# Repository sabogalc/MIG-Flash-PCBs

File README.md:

# MIG Flash PCBs & Models
This repository hosts KiCad projects and 3D printable replacement parts for the MIG Dumper and Flashcart PCBs. These files should prove very useful towards understanding the inner workings of the devices, especially with the schematics and boardview files. As-is, not much can be done with the board files since the original boards are programmed at the factory. The only way to currently get a working board from these files is by transplanting at minimum the FPGA and the microcontroller from an OEM MIG device to the new board.

> 
> The 8 pins seen above the USB-C port and to the right of the microcontroller in this photo are the ones used to program the board at the factory (see https://docs.espressif.com/projects/esp-idf/en/v5.2/esp32s2/api-guides/dfu.html for more information)

> 
> The flashcart PCB inside of the game enclosure.

Another useful resource found in this repo is the bill of materials for both devices. If you have a MIG device but a part on it has gone bad or is missing, this repository should assist with finding replacement resistors or capacitors of the correct value, or finding part numbers for components such as the toggle button on the Flashcart. For more information on either board, see their folders in the `KiCad Projects` directory.

The 3D models are compatible with original hardware and the PCBs in this repository. The recommended screws for the dumper are M2x8 and for the cartridge shell are M1.2x2. Both may printed in filament or resin, though resin is recommended for the cartridge shell to better reproduce sub-mm features.

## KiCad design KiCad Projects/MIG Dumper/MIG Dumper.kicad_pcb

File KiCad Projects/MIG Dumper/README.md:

# MIG Dumper

### Overview
This is a very straightforward board design. The FPGA is is the first point of contact with the cartridge, and it takes care of direct communication with the data and clock lines in order to be able to read the onboard cartridge data. The microcontroller then takes this data from the FPGA, and it relays it to the SD card to USB adapter, presumably through SPI (reference [here](https://switchbrew.org/wiki/Gamecard#Protocol)). With data moving to and from the FPGA/microcontroller in SPI, it is very simple to configure the board as if it were reading an SD card, after which the dumper allows the files to be read by any USB-enabled device.

### Ordering Specifications
The original board is a standard 1.6mm thick board, and all other options (soldermask, surface finish, etc.) can be customized to your liking. Please note that if you are using the OEM enclosure, the 4.7uF capacitor for C29 in the included Digikey/Mouser BOMs is too tall to allow for it to fully close. The capacitor on the original board is 0.85mm tall, but the one I included is 1.6mm tall.

### Component Measurements and BOM Discrepancies
I measured the components to the best of my ability, but there may be slight discrepancies. For example, the aforementioned 4.7uF capacitor was read in real life to be 4.5uF, but I could not find a 1206 4.5uF capacitor on either Digikey or Mouser. As such, the BOMs have some substitutions, such as 100nF capacitors instead of 110nF capacitors, but the measurements in the schematic and PCB are what most align with what I measured in real life. For capacitors in the pF range that I could not measure, I referenced the datasheets for the [ECS-400-10-37B2-CKY-TR](https://ecsxtal.com/store/pdf/ECX-1637B2.pdf) and [MAX20022ATIA+](https://www.analog.com/media/en/technical-documentation/data-sheets/max20021-max20022.pdf) to obtain these values.

Additionally, the SD card to USB adapter chip and the cartridge reader are not present in the BOMs because neither part is available on Digikey or Mouser, but you can purchase both of them from AliExpress.

[GL823K-HCY04 chip](https://www.aliexpress.com/item/3256805047594623.html)

[Cartridge reader](https://www.aliexpress.com/item/3256804487003304.html)

### Can I use these designs to manufacture my own MIG Dumper?
Yes and no. I have succesfully transplanted all the parts of an original Dumper to this PCB, and it works perfectly. Building it from scratch with the parts from the included `.csv` and `.xlsx` BOMs does not work, but if you substitute in an OEM FPGA and ESP32, then it works. This is because the firmware for these chips is programmed and encrypted at the factory, as specified in the main landing page's `README`.

While it may be possible to break this encryption (see [here](https://hackaday.com/2024/01/15/breaking-the-flash-encryption-feature-of-espressifs-microcontrollers/)), I am a hardware engineer and not very interested in delving into the firmware side of things. However, I will include a schematic for a programmer board below should anyone want to embark on that journey. The instructions for the boot sequence needed are found at https://docs.espressif.com/projects/esp-idf/en/v5.2/esp32s2/api-guides/dfu.html in the bootloader mode note.

Below is a photo of the board from this repository screwed into the enclosure and reading a gamecard.

### KiCad 3D View
Below are screenshots of the board from KiCad's 3D board viewer.

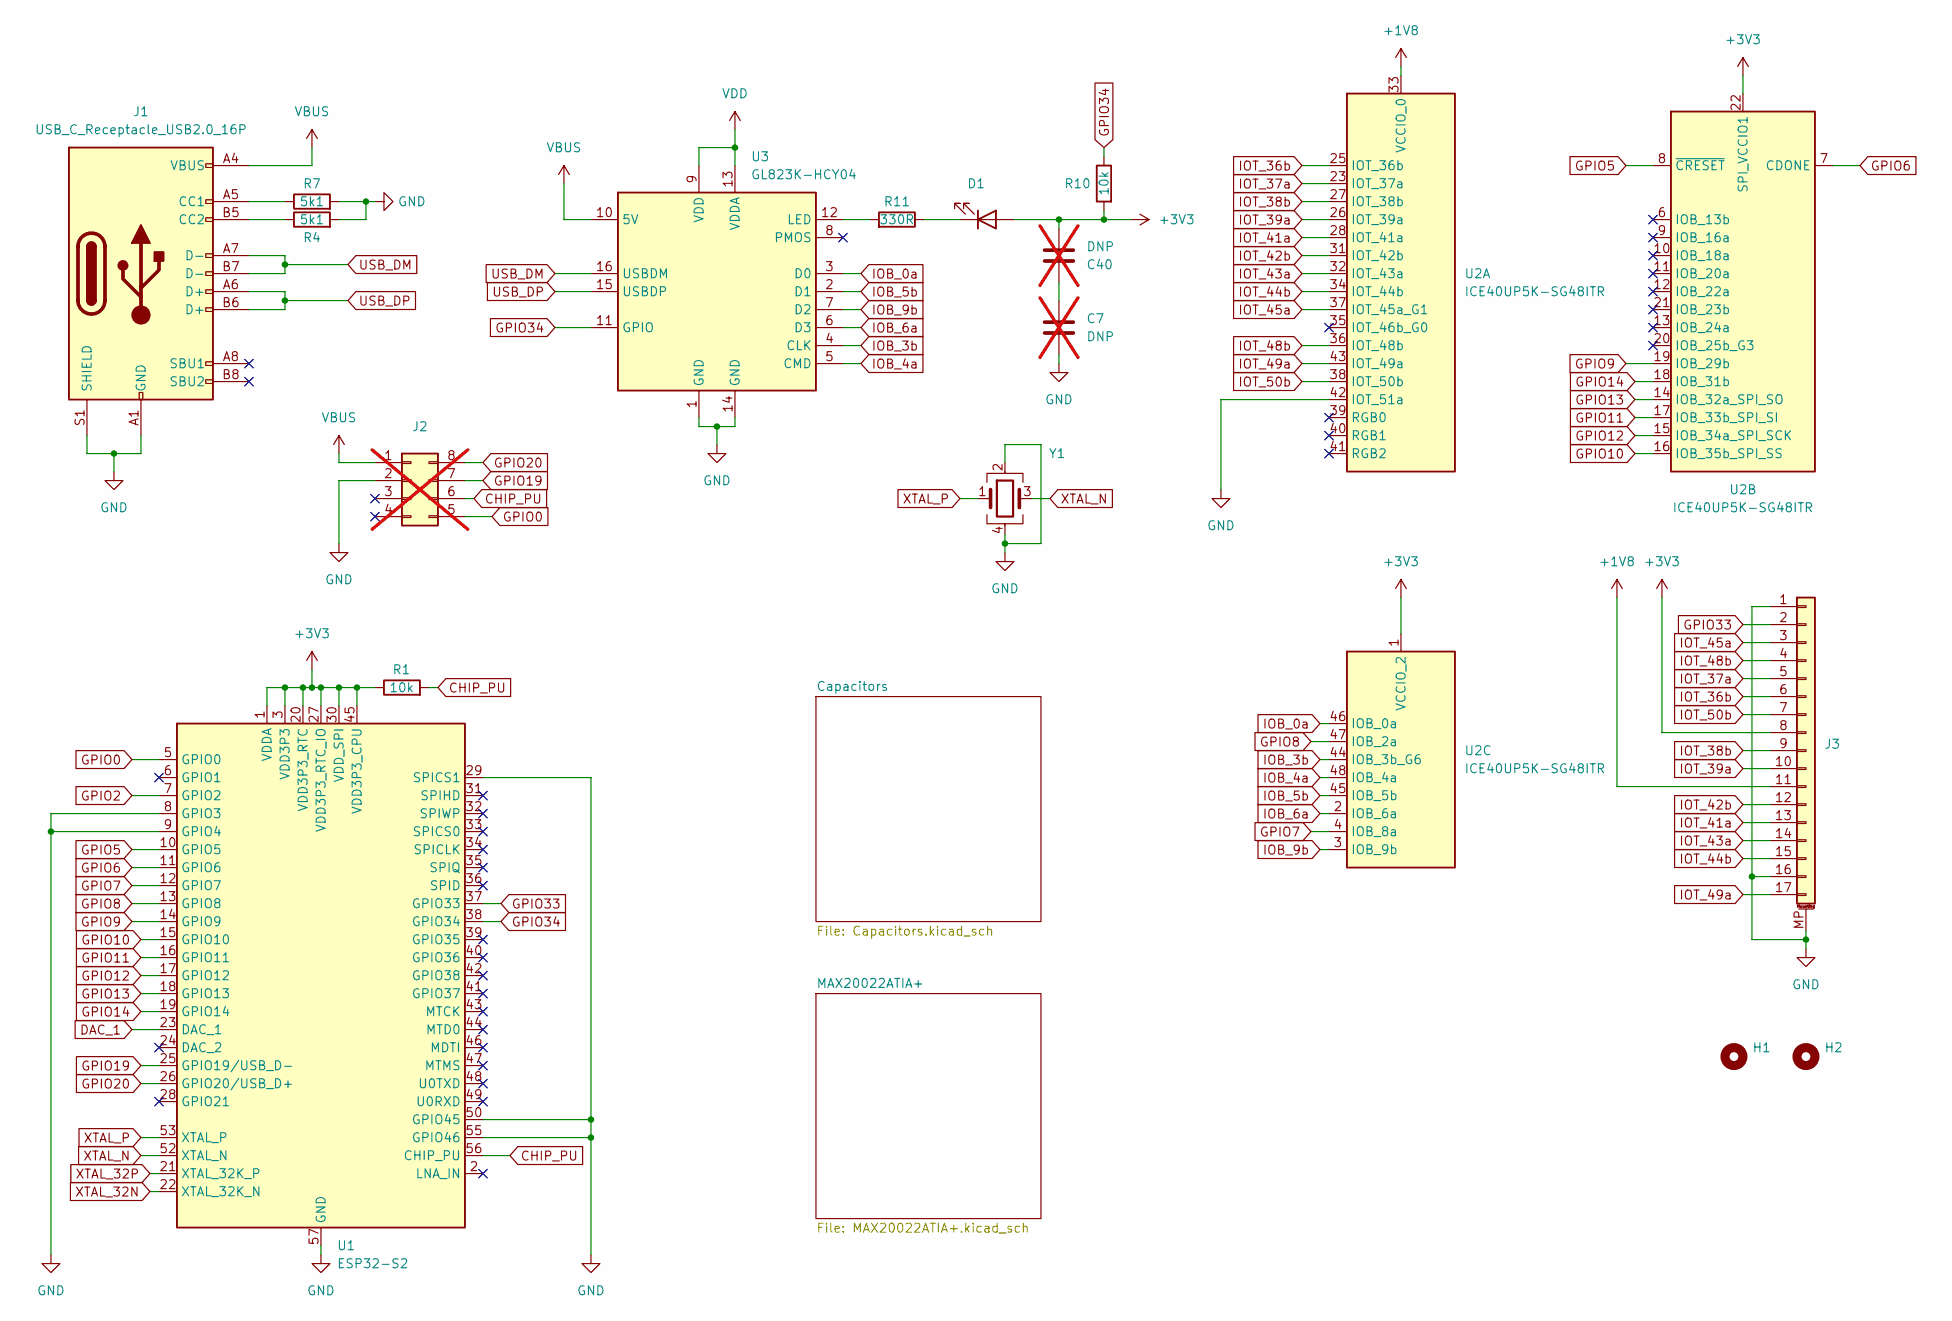
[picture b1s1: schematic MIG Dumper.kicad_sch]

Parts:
C7: DNP; C_1206_3216Metric_Pad1.33x1.80mm_HandSolder; not fitted
C40: DNP; C_0603_1608Metric; not fitted
D1: APT3216LSECK/J3-PRV; LED_1206_3216Metric_Pad1.42x1.75mm_HandSolder
H1, H2: MountingHole; MountingHole_2.2mm_M2_DIN965_Pad_TopBottom
J1: USB_C_Receptacle_USB2.0_16P; USB_C_Receptacle_GCT_USB4105-xx-A_16P_TopMnt_Horizontal
J2: Conn_02x04_Counter_Clockwise; PinHeader_2x04_P1.27mm_Vertical; not fitted
J3: Conn_01x17_MountingPin; Switch_Cartridge
R1, R10: 10k; R_0603_1608Metric
R4, R7: 5k1; R_0603_1608Metric
R11: 330R; R_0603_1608Metric
U1: ESP32-S2; QFN-56-1EP_7x7mm_P0.4mm_EP4x4mm
U2: ICE40UP5K-SG48ITR; QFN-48-1EP_7x7mm_P0.5mm_EP5.15x5.15mm
U3: GL823K-HCY04; SSOP-16_3.9x4.9mm_P0.635mm
Y1: ECS-400-10-37B2-CKY-TR; Crystal_SMD_SeikoEpson_FA128-4Pin_2.0x1.6mm

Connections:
+1V8: J3.11, U2.33 (VCCIO_0); also elsewhere on the board
+3V3: C40.2, D1.2 (A), J3.8, R1.1, R10.2, U1.1 (VDDA), U1.3 (VDD3P3), U1.4 (VDD3P3), U1.20 (VDD3P3_RTC), U1.27 (VDD3P3_RTC_IO), U1.30 (VDD_SPI), U1.45 (VDD3P3_CPU), U1.51 (VDDA), U1.54 (VDDA), U2.1 (VCCIO_2), U2.22 (SPI_VCCIO1); also elsewhere on the board
CHIP_PU: J2.6, R1.2, U1.56 (CHIP_PU)
DAC_1: U1.23 (DAC_1); also elsewhere on the board
GND: C7.2, J1.A1 (GND), J1.A12 (GND), J1.B1 (GND), J1.B12 (GND), J1.S1 (SHIELD), J2.2, J3.1, J3.16, J3.MP (MountPin), R4.2, R7.2, U1.8 (GPIO3), U1.9 (GPIO4), U1.29 (SPICS1), U1.50 (GPIO45), U1.55 (GPIO46), U1.57 (GND), U2.42 (IOT_51a), U3.1 (GND), U3.14 (GND), Y1.2, Y1.4; also elsewhere on the board
GPIO0: J2.5, U1.5 (GPIO0)
GPIO2: U1.7 (GPIO2); also elsewhere on the board
GPIO5: U1.10 (GPIO5), U2.8 (~CRESET)
GPIO6: U1.11 (GPIO6), U2.7 (CDONE)
GPIO7: U1.12 (GPIO7), U2.4 (IOB_8a)
GPIO8: U1.13 (GPIO8), U2.47 (IOB_2a)
GPIO9: U1.14 (GPIO9), U2.19 (IOB_29b)
GPIO10: U1.15 (GPIO10), U2.16 (IOB_35b_SPI_SS)
GPIO11: U1.16 (GPIO11), U2.17 (IOB_33b_SPI_SI)
GPIO12: U1.17 (GPIO12), U2.15 (IOB_34a_SPI_SCK)
GPIO13: U1.18 (GPIO13), U2.14 (IOB_32a_SPI_SO)
GPIO14: U1.19 (GPIO14), U2.18 (IOB_31b)
GPIO19: J2.7, U1.25 (GPIO19/USB_D-)
GPIO20: J2.8, U1.26 (GPIO20/USB_D+)
GPIO33: J3.2, U1.37 (GPIO33)
GPIO34: R10.1, U1.38 (GPIO34), U3.11 (GPIO)
IOB_0a: U2.46 (IOB_0a), U3.3 (D0)
IOB_3b: U2.44 (IOB_3b_G6), U3.4 (CLK)
IOB_4a: U2.48 (IOB_4a), U3.5 (CMD)
IOB_5b: U2.45 (IOB_5b), U3.2 (D1)
IOB_6a: U2.2 (IOB_6a), U3.6 (D3)
IOB_9b: U2.3 (IOB_9b), U3.7 (D2)
IOT_36b: J3.6, U2.25 (IOT_36b)
IOT_37a: J3.5, U2.23 (IOT_37a)
IOT_38b: J3.9, U2.27 (IOT_38b)
IOT_39a: J3.10, U2.26 (IOT_39a)
IOT_41a: J3.13, U2.28 (IOT_41a)
IOT_42b: J3.12, U2.31 (IOT_42b)
IOT_43a: J3.14, U2.32 (IOT_43a)
IOT_44b: J3.15, U2.34 (IOT_44b)
IOT_45a: J3.3, U2.37 (IOT_45a_G1)
IOT_48b: J3.4, U2.36 (IOT_48b)
IOT_49a: J3.17, U2.43 (IOT_49a)
IOT_50b: J3.7, U2.38 (IOT_50b)
unnamed: C7.1, C40.1
unnamed: D1.1 (K), R11.1
unnamed: J1.A5 (CC1), R7.1
unnamed: J1.B5 (CC2), R4.1
unnamed: R11.2, U3.12 (LED)
USB_DM: J1.A7 (D-), J1.B7 (D-), U3.16 (USBDM)
USB_DP: J1.A6 (D+), J1.B6 (D+), U3.15 (USBDP)
VBUS: J1.A4 (VBUS), J1.A9 (VBUS), J1.B4 (VBUS), J1.B9 (VBUS), J2.1, U3.10 (5V); also elsewhere on the board
VDD: U3.9 (VDD), U3.13 (VDDA); also elsewhere on the board
XTAL_32N: U1.22 (XTAL_32K_N); also elsewhere on the board
XTAL_32P: U1.21 (XTAL_32K_P); also elsewhere on the board
XTAL_N: U1.52 (XTAL_N), Y1.3; also elsewhere on the board
XTAL_P: U1.53 (XTAL_P), Y1.1; also elsewhere on the board

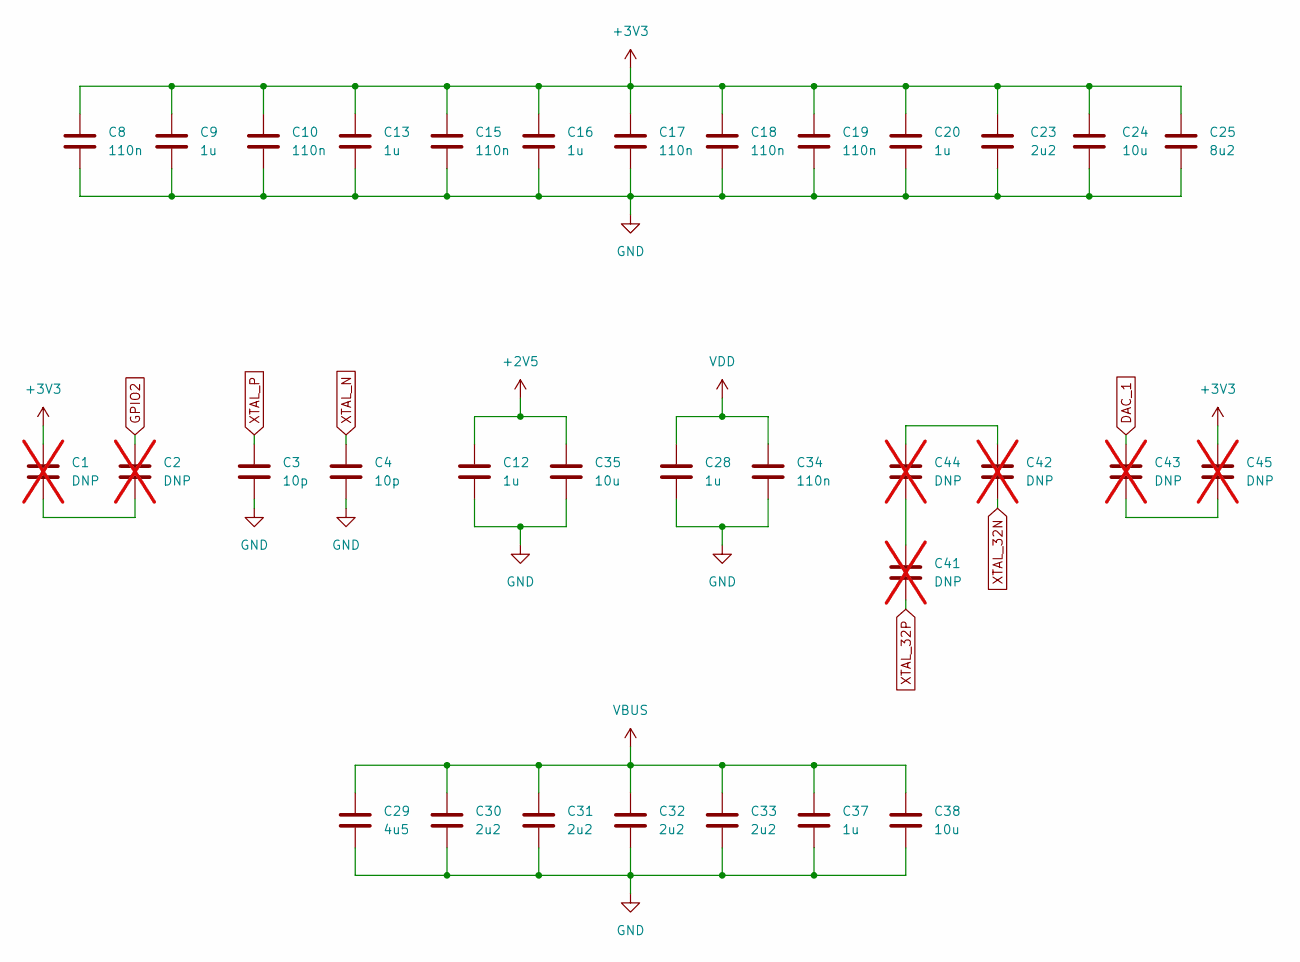
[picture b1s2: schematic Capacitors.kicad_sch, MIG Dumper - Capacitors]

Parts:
C1: DNP; C_1206_3216Metric_Pad1.33x1.80mm_HandSolder; not fitted
C2, C41, C42, C43: DNP; C_0603_1608Metric; not fitted
C3, C4: 10p; C_0603_1608Metric
C8, C10, C15, C17, C18, C19, C34: 110n; C_0603_1608Metric
C9, C12, C13, C16, C20, C28, C37: 1u; C_0603_1608Metric
C23, C30, C31, C32, C33: 2u2; C_0603_1608Metric
C24, C35, C38: 10u; C_1206_3216Metric_Pad1.33x1.80mm_HandSolder
C25: 8u2; C_1206_3216Metric_Pad1.33x1.80mm_HandSolder
C29: 4u5; C_1206_3216Metric_Pad1.33x1.80mm_HandSolder
C44, C45: DNP; C_0201_0603Metric; not fitted

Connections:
+2V5: C12.1, C35.1; also elsewhere on the board
+3V3: C1.1, C8.1, C9.1, C10.1, C13.1, C15.1, C16.1, C17.1, C18.1, C19.1, C20.1, C23.1, C24.1, C25.1, C45.1; also elsewhere on the board
DAC_1: C43.2; also elsewhere on the board
GND: C3.2, C4.2, C8.2, C9.2, C10.2, C12.2, C13.2, C15.2, C16.2, C17.2, C18.2, C19.2, C20.2, C23.2, C24.2, C25.2, C28.2, C29.2, C30.2, C31.2, C32.2, C33.2, C34.2, C35.2, C37.2, C38.2; also elsewhere on the board
GPIO2: C2.1; also elsewhere on the board
unnamed: C1.2, C2.2
unnamed: C41.1, C44.1
unnamed: C42.1, C44.2
unnamed: C43.1, C45.2
VBUS: C29.1, C30.1, C31.1, C32.1, C33.1, C37.1, C38.1; also elsewhere on the board
VDD: C28.1, C34.1; also elsewhere on the board
XTAL_32N: C42.2; also elsewhere on the board
XTAL_32P: C41.2; also elsewhere on the board
XTAL_N: C4.1; also elsewhere on the board
XTAL_P: C3.1; also elsewhere on the board

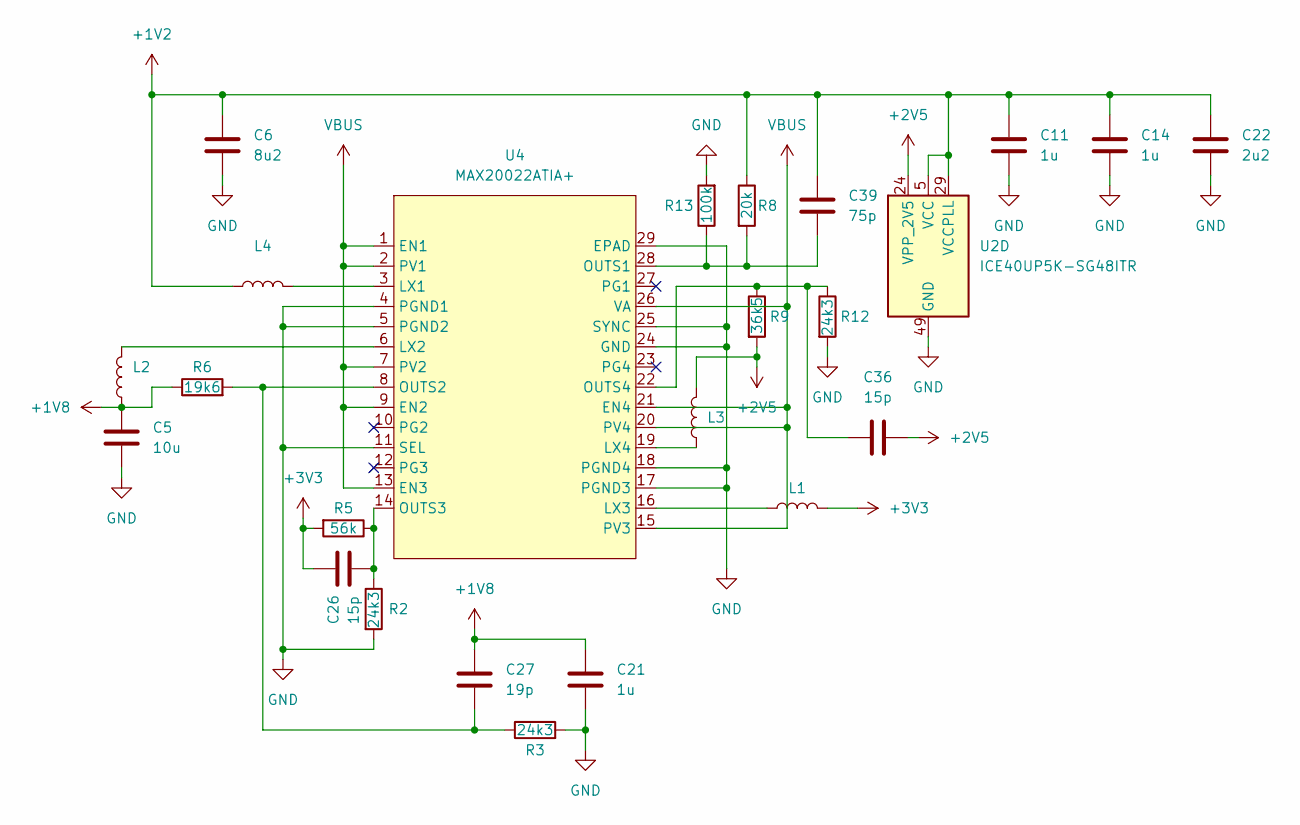
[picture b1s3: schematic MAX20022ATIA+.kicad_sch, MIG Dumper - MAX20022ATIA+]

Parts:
C5: 10u; C_1206_3216Metric_Pad1.33x1.80mm_HandSolder
C6: 8u2; C_1206_3216Metric_Pad1.33x1.80mm_HandSolder
C11, C14, C21: 1u; C_0603_1608Metric
C22: 2u2; C_0603_1608Metric
C26, C36: 15p; C_0603_1608Metric
C27: 19p; C_0603_1608Metric
C39: 75p; C_0603_1608Metric
L1, L2, L3, L4: LQM21PN1R5MEHD; L_0805_2012Metric_Pad1.15x1.40mm_HandSolder
R2, R3, R12: 24k3; R_0603_1608Metric
R5: 56k; R_0603_1608Metric
R6: 19k6; R_0603_1608Metric
R8: 20k; R_0603_1608Metric
R9: 36k5; R_0603_1608Metric
R13: 100k; R_0603_1608Metric
U2: ICE40UP5K-SG48ITR; QFN-48-1EP_7x7mm_P0.5mm_EP5.15x5.15mm
U4: MAX20022ATIA+; TQFN-28-1EP_5x5mm_P0.5mm_EP2.7x2.7mm

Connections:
+1V2: C6.1, C11.1, C14.1, C22.1, C39.1, L4.1, R8.1, U2.5 (VCC), U2.29 (VCCPLL), U2.30 (VCC)
+1V8: C5.1, C21.1, C27.1, L2.1, R6.1; also elsewhere on the board
+2V5: C36.1, L3.2, R9.2, U2.24 (VPP_2V5); also elsewhere on the board
+3V3: C26.1, L1.2, R5.2; also elsewhere on the board
GND: C5.2, C6.2, C11.2, C14.2, C21.2, C22.2, R2.2, R3.2, R12.2, R13.2, U2.49 (GND), U4.4 (PGND1), U4.5 (PGND2), U4.11 (SEL), U4.17 (PGND3), U4.18 (PGND4), U4.24 (GND), U4.25 (SYNC), U4.29 (EPAD); also elsewhere on the board
unnamed: L4.2, U4.3 (LX1)
unnamed: L2.2, U4.6 (LX2)
unnamed: L1.1, U4.16 (LX3)
unnamed: L3.1, U4.19 (LX4)
unnamed: C39.2, R8.2, R13.1, U4.28 (OUTS1)
unnamed: C27.2, R3.1, R6.2, U4.8 (OUTS2)
unnamed: C26.2, R2.1, R5.1, U4.14 (OUTS3)
unnamed: C36.2, R9.1, R12.1, U4.22 (OUTS4)
VBUS: U4.1 (EN1), U4.2 (PV1), U4.7 (PV2), U4.9 (EN2), U4.13 (EN3), U4.15 (PV3), U4.20 (PV4), U4.21 (EN4), U4.26 (VA); also elsewhere on the board

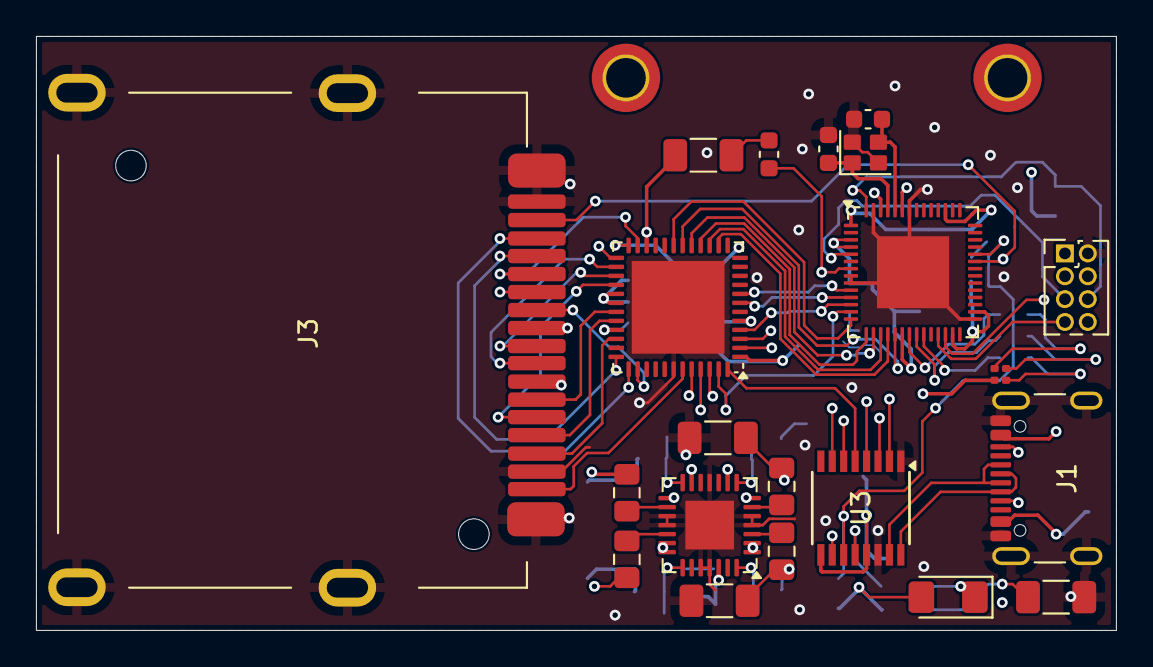
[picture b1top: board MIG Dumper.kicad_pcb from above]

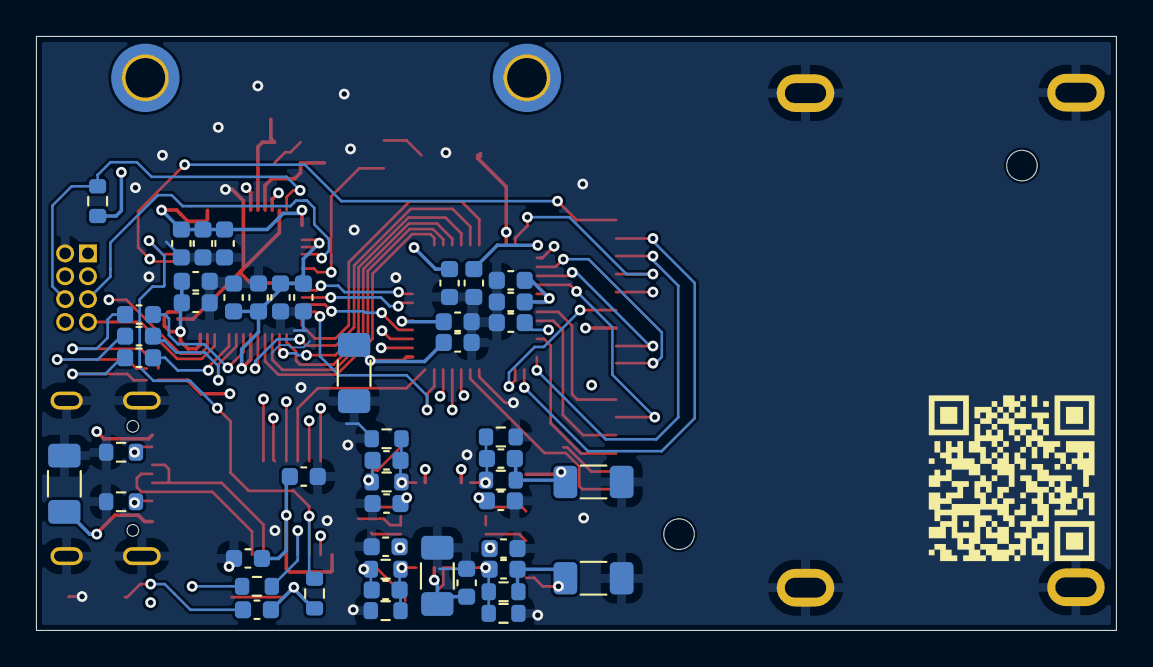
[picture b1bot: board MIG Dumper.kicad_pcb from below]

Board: 4 copper layers, 60.0 x 33.0 mm, 73 parts (49 on the bottom side), 66 nets.

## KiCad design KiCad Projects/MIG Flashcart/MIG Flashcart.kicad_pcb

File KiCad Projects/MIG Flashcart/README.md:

# MIG Flashcart

### Overview
The Flashcart board is very compact, and it is a bit challenging to solder it by hand. Most of the passive components are the 0201 size, and the 0404 RGB LED in the top right is also extremely small. Additionally, the vias have been trimmed down to a 0.2mm size to accommodate the board's routing.

A series of leaks in July 2021 made the low-level hardware of the Switch game cartridge reader public, and it is powered by an ASIC called [Lotus3](https://switchbrew.org/wiki/Lotus3). I don't know much about how this chip/protocol works, but the FPGA and microcontroller in this flashcart are programmed to communicate on this custom interface. 

### Ordering Specifications
To ensure this board fits in the game enclosure and that it can be read, it should be ordered as a 0.8mm thick board with an ENIG finish. All other options can be left as their default.

### Component Measurements and BOM Discrepancies
I measured the components to the best of my ability, but there may be slight discrepancies. For example, I found it odd that 12 of the capacitors measured as 0.82uF and 4 of them measured as 0.88uF. I suspect that all of them are 0.82uF, and imperfections in the measurements caused the 4 outliers to read higher values. Even so, they were consistently measuring high enough that I felt it best to mark them as 0.88uF in the schematic. This point is a bit moot, however, because I could not find any 0201 capacitors on either Digikey or Mouser for 0.82uF or 0.88uF. As such, the BOMs have some substitutions, such as 1uF capacitors in place of the 0.82uF and 0.88uF ones, but the measurements in the schematic and PCB are what most align with what I measured in real life.

### Can I use these designs to manufacture my own MIG Flashcart?
The answer is the same as in [the corresponding section of the Dumper's README](https://github.com/sabogalc/MIG-Flash-PCBs/tree/main/KiCad%20Projects/MIG%20Dumper#can-i-use-these-designs-to-manufacture-my-own-mig-dumper). Due to the firmware encryption on the original boards, making this board from scratch (e.g. without transplanting the original μC and FPGA) proves to be a bit of a challenge.

Importantly though, the programmer board schematic I made for the Dumper will not work for the Flashcart as-is since the Flashcart has no 5V/VBUS signal. The programmer board would need to be modified to have an onboard 3.3V regulator, and then with this signal on the Flashcart's VCC breakout signal, it should work. Should anyone make that programmer board and want to write their own firmware, the instructions for accomplishing this can be found on [Espressif's website in the bootloader mode note](https://docs.espressif.com/projects/esp-idf/en/v5.2/esp32s2/api-guides/dfu.html).

I have assembled this board with parts from the included BOM and confirmed that it works when using the chips from an OEM MIG Flashcart. If you are using the parts from the BOM, the LED has a pin 1 indicator which I will show in a photo below. Make sure that the white squre between the two gold pins is facing into the board towards the crystal oscillator.

Below are some photos of the board from this repository in the flashcart enclosure.

> 
> The cartridge reading a game in the Switch and showing a green status LED.

### KiCad 3D View
Below are screenshots of the board from KiCad's 3D board viewer.

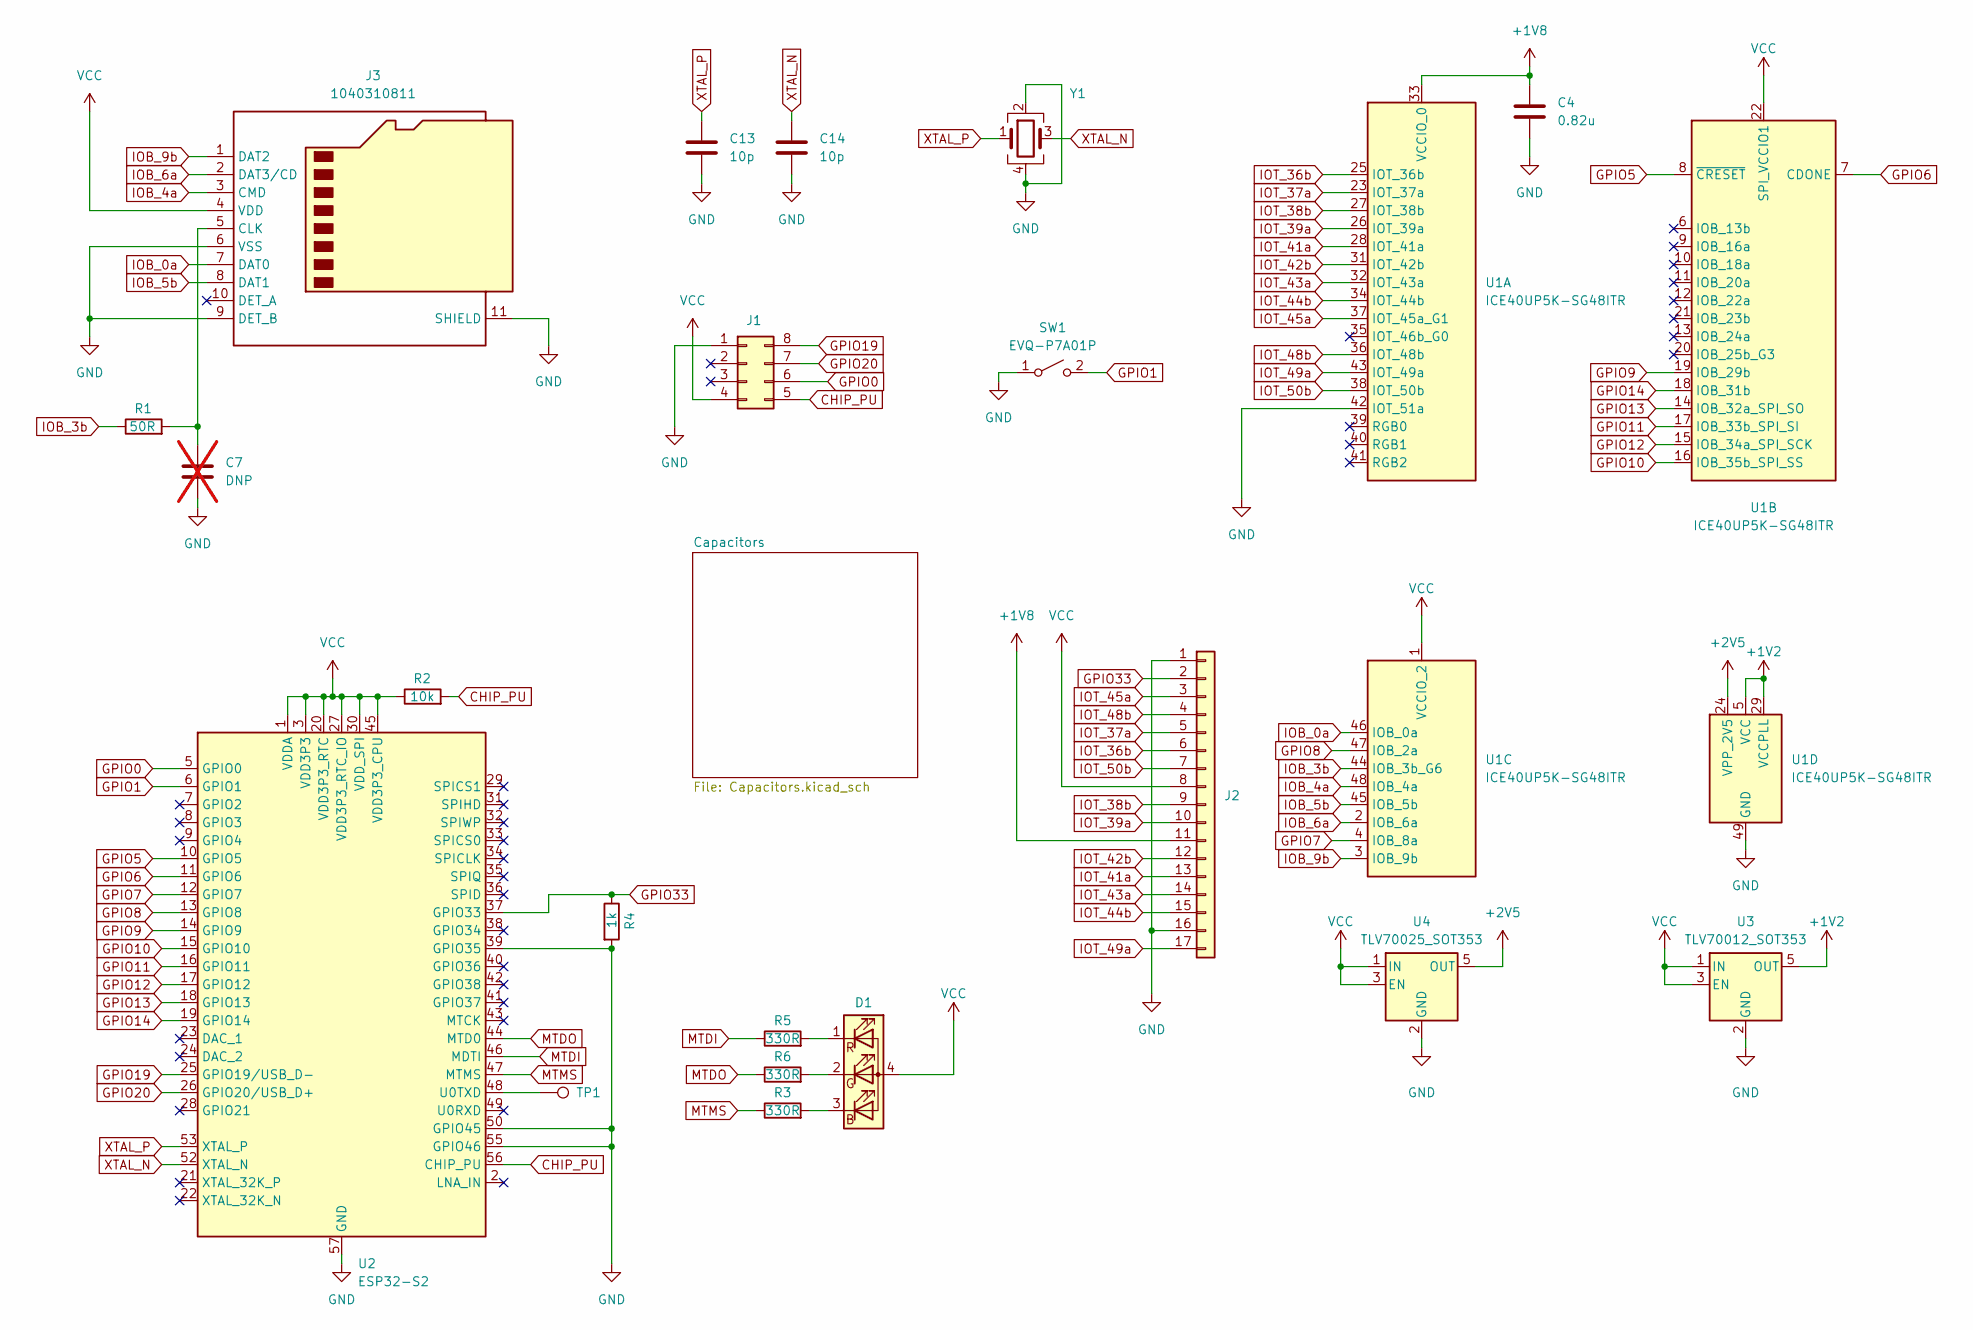
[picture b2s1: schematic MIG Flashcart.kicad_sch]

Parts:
C4: 0.82u; C_0201_0603Metric
C7: DNP; C_0201_0603Metric; not fitted
C13, C14: 10p; C_0201_0603Metric
D1: UHD111A-FKA-C3K23E1L3VG5ZB3Z3; SMD4_UHD111A-FKA_CRW
J1: Conn_02x04_Counter_Clockwise; PinSocket_2x04_P1.27mm_Vertical_SMD
J2: Conn_01x17; Cartridge_Pins
J3: 1040310811; microSD_HC_Molex_104031-0811
R1: 50R; R_0201_0603Metric
R2: 10k; R_0201_0603Metric
R3, R5, R6: 330R; R_0201_0603Metric
R4: 1k; R_0201_0603Metric
SW1: EVQ-P7A01P; SW_SPST_EVQP7A
TP1: TestPoint; TestPoint_Pad_D0.5mm
U1: ICE40UP5K-SG48ITR; QFN-48-1EP_7x7mm_P0.5mm_EP5.15x5.15mm
U2: ESP32-S2; QFN-56-1EP_7x7mm_P0.4mm_EP4x4mm
U3: TLV70012_SOT353; SOT-353_SC-70-5
U4: TLV70025_SOT353; SOT-353_SC-70-5
Y1: ECS-400-10-37B2-CKY-TR; Crystal_SMD_SeikoEpson_FA128-4Pin_2.0x1.6mm

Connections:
+1V2: U1.5 (VCC), U1.29 (VCCPLL), U1.30 (VCC), U3.5 (OUT); also elsewhere on the board
+1V8: C4.1, J2.11, U1.33 (VCCIO_0)
+2V5: U1.24 (VPP_2V5), U4.5 (OUT); also elsewhere on the board
CHIP_PU: J1.5, R2.2, U2.56 (CHIP_PU)
GND: C4.2, C7.2, C13.2, C14.2, J1.1, J2.1, J2.16, J3.6 (VSS), J3.9 (DET_B), J3.11 (SHIELD), R4.2, SW1.1 (A), U1.42 (IOT_51a), U1.49 (GND), U2.39 (GPIO35), U2.50 (GPIO45), U2.55 (GPIO46), U2.57 (GND), U3.2 (GND), U4.2 (GND), Y1.2, Y1.4; also elsewhere on the board
GPIO0: J1.6, U2.5 (GPIO0)
GPIO1: SW1.2 (B), U2.6 (GPIO1)
GPIO5: U1.8 (~CRESET), U2.10 (GPIO5)
GPIO6: U1.7 (CDONE), U2.11 (GPIO6)
GPIO7: U1.4 (IOB_8a), U2.12 (GPIO7)
GPIO8: U1.47 (IOB_2a), U2.13 (GPIO8)
GPIO9: U1.19 (IOB_29b), U2.14 (GPIO9)
GPIO10: U1.16 (IOB_35b_SPI_SS), U2.15 (GPIO10)
GPIO11: U1.17 (IOB_33b_SPI_SI), U2.16 (GPIO11)
GPIO12: U1.15 (IOB_34a_SPI_SCK), U2.17 (GPIO12)
GPIO13: U1.14 (IOB_32a_SPI_SO), U2.18 (GPIO13)
GPIO14: U1.18 (IOB_31b), U2.19 (GPIO14)
GPIO19: J1.8, U2.25 (GPIO19/USB_D-)
GPIO20: J1.7, U2.26 (GPIO20/USB_D+)
GPIO33: J2.2, R4.1, U2.37 (GPIO33)
IOB_0a: J3.7 (DAT0), U1.46 (IOB_0a)
IOB_3b: R1.1, U1.44 (IOB_3b_G6)
IOB_4a: J3.3 (CMD), U1.48 (IOB_4a)
IOB_5b: J3.8 (DAT1), U1.45 (IOB_5b)
IOB_6a: J3.2 (DAT3/CD), U1.2 (IOB_6a)
IOB_9b: J3.1 (DAT2), U1.3 (IOB_9b)
IOT_36b: J2.6, U1.25 (IOT_36b)
IOT_37a: J2.5, U1.23 (IOT_37a)
IOT_38b: J2.9, U1.27 (IOT_38b)
IOT_39a: J2.10, U1.26 (IOT_39a)
IOT_41a: J2.13, U1.28 (IOT_41a)
IOT_42b: J2.12, U1.31 (IOT_42b)
IOT_43a: J2.14, U1.32 (IOT_43a)
IOT_44b: J2.15, U1.34 (IOT_44b)
IOT_45a: J2.3, U1.37 (IOT_45a_G1)
IOT_48b: J2.4, U1.36 (IOT_48b)
IOT_49a: J2.17, U1.43 (IOT_49a)
IOT_50b: J2.7, U1.38 (IOT_50b)
MTDI: R5.1, U2.46 (MDTI)
MTDO: R6.1, U2.44 (MTD0)
MTMS: R3.1, U2.47 (MTMS)
unnamed: D1.3 (BK), R3.2
unnamed: D1.2 (GK), R6.2
unnamed: D1.1 (RK), R5.2
unnamed: C7.1, J3.5 (CLK), R1.2
unnamed: TP1.1, U2.48 (U0TXD)
VCC: D1.4 (A), J1.4, J2.8, J3.4 (VDD), R2.1, U1.1 (VCCIO_2), U1.22 (SPI_VCCIO1), U2.1 (VDDA), U2.3 (VDD3P3), U2.4 (VDD3P3), U2.20 (VDD3P3_RTC), U2.27 (VDD3P3_RTC_IO), U2.30 (VDD_SPI), U2.45 (VDD3P3_CPU), U2.51 (VDDA), U2.54 (VDDA), U3.1 (IN), U3.3 (EN), U4.1 (IN), U4.3 (EN); also elsewhere on the board
XTAL_N: C14.1, U2.52 (XTAL_N), Y1.3
XTAL_P: C13.1, U2.53 (XTAL_P), Y1.1

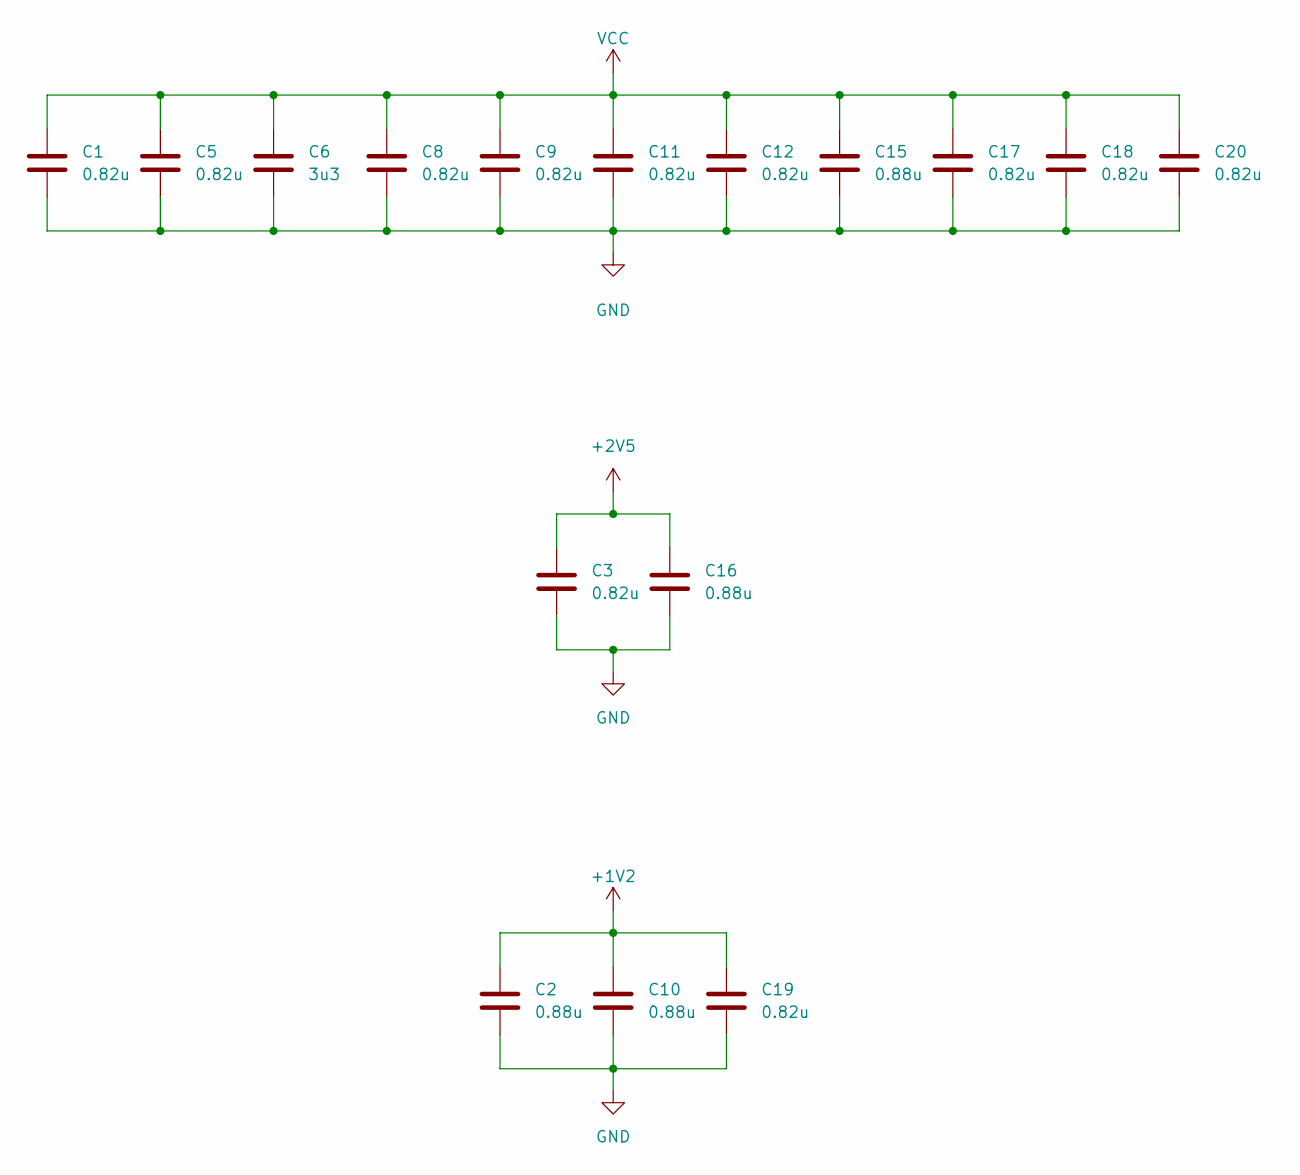
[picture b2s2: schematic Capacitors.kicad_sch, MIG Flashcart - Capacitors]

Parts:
C1, C3, C5, C8, C9, C11, C12, C17, C18, C19, C20: 0.82u; C_0201_0603Metric
C2, C10, C15, C16: 0.88u; C_0201_0603Metric
C6: 3u3; C_0402_1005Metric

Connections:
+1V2: C2.1, C10.1, C19.1; also elsewhere on the board
+2V5: C3.1, C16.1; also elsewhere on the board
GND: C1.2, C2.2, C3.2, C5.2, C6.2, C8.2, C9.2, C10.2, C11.2, C12.2, C15.2, C16.2, C17.2, C18.2, C19.2, C20.2; also elsewhere on the board
VCC: C1.1, C5.1, C6.1, C8.1, C9.1, C11.1, C12.1, C15.1, C17.1, C18.1, C20.1; also elsewhere on the board

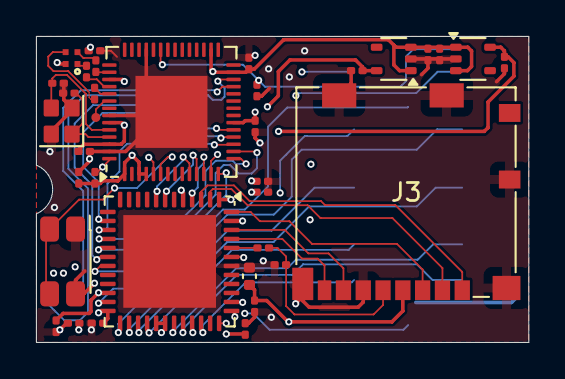
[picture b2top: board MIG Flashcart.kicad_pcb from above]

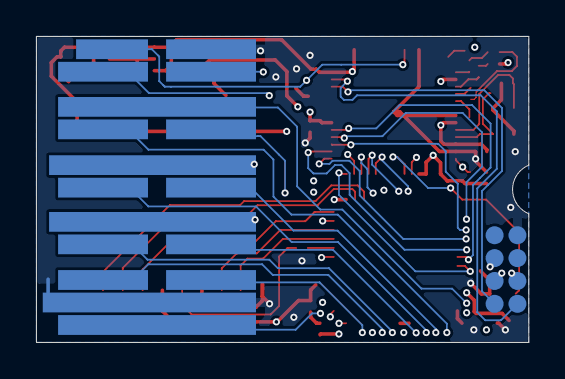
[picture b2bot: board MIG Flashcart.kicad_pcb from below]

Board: 4 copper layers, 27.4 x 17.0 mm, 37 parts (2 on the bottom side), 49 nets.

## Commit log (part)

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2024-10-18 Initial commit
    First commit including KiCad project files and boardview files for both the MIG Flashcart and Dumper.
2024-11-22 Updated Flashcart PCB, uploaded Flashcart BOM
    Revised the Flashcart PCB to the newer revision of the MIG v2, as well as added DigiKey and Mouser BOMs for the Flashcart. One capacitor measurement on the Dumper PCB was corrected as well.
2025-07-16 Updated READMEs
    Updated READMEs to indicate that the flashcart PCB has been confirmed to work. Also updated the boardview README since the obdata script has been upstreamed.
